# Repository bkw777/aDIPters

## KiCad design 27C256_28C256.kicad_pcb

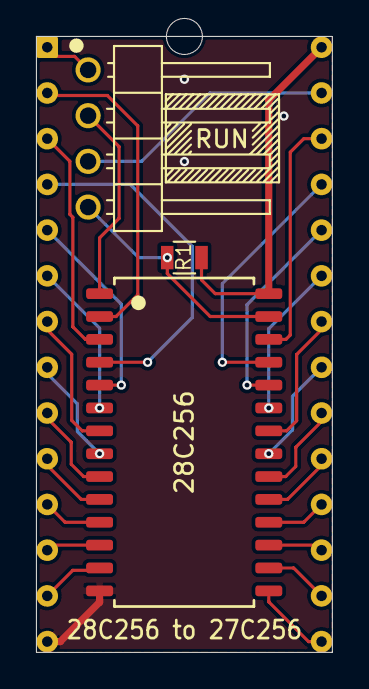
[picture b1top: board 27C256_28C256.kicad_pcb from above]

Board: 2 copper layers, 16.4 x 34.2 mm, 4 parts (0 on the bottom side), 30 nets.

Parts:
J1: 27C256 DIP LEGS; DIP-28_W15.24mm_pcb_sil_pins
JP1: Jumper_3_Bridged12; Pin_Header_Angled_1x04_Pitch2.54mm
R1: 47k; R_0805
U1: 28C256; SOIC28W

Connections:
/A0: J1.10, U1.10
/A1: J1.9, U1.9
/A2: J1.8, U1.8
/A3: J1.7, U1.7
/A4: J1.6, U1.6
/A5: J1.5, U1.5
/A6: J1.4, U1.4
/A7: J1.3, U1.3
/A8: J1.25, U1.25
/A9: J1.24, U1.24
/A10: J1.21, U1.21
/A11: J1.23, U1.23
/A12: J1.2, U1.2
/A13: J1.26, U1.26
/A14: JP1.2, U1.1
/A14_WE: J1.27, JP1.3
/D0: J1.11, U1.11
/D1: J1.12, U1.12
/D2: J1.13, U1.13
/D3: J1.15, U1.15
/D4: J1.16, U1.16
/D5: J1.17, U1.17
/D6: J1.18, U1.18
/D7: J1.19, U1.19
/GND: J1.14, U1.14
/NC_A14: J1.1, JP1.1
/VCC: J1.28, R1.2, U1.28
/~CE: J1.20, U1.20
/~OE: J1.22, U1.22
/~WE: JP1.4, R1.1, U1.27

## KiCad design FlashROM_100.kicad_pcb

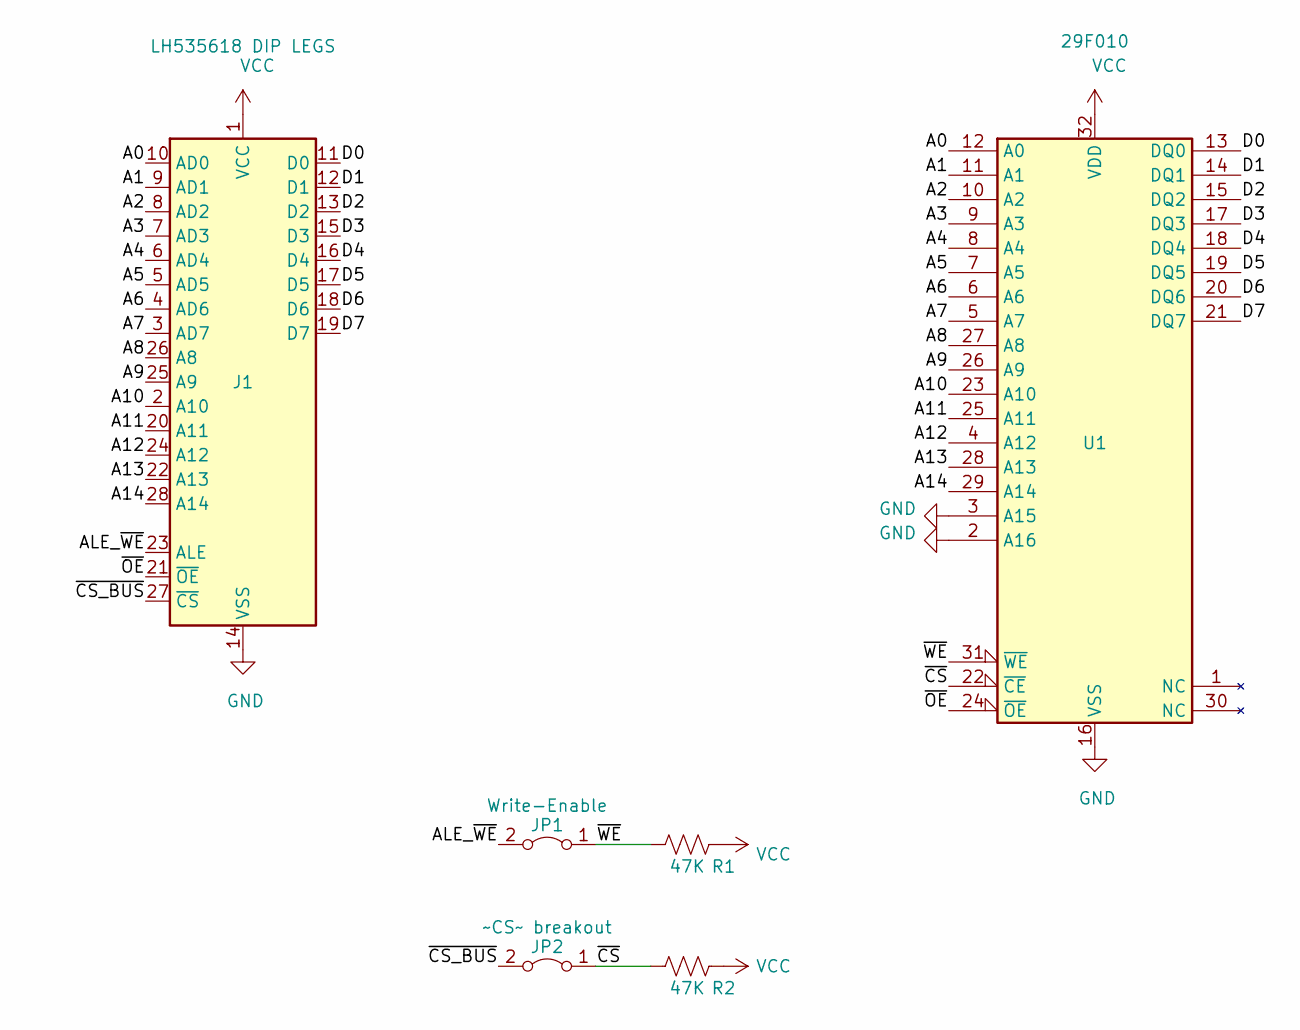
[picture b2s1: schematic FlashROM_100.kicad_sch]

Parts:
J1: LH535618 DIP LEGS; DIP28_0.6_pcb
JP1: Write-Enable; Pin_Header_Angled_1x02_Pitch2.54mm
JP2: ~CS~ breakout; Pin_Header_Angled_1x02_Pitch2.54mm
R1, R2: 47K; R_0805
U1: 29F010; PLCC32_7x9

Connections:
/A0: J1.10 (AD0), U1.12 (A0)
/A1: J1.9 (AD1), U1.11 (A1)
/A2: J1.8 (AD2), U1.10 (A2)
/A3: J1.7 (AD3), U1.9 (A3)
/A4: J1.6 (AD4), U1.8 (A4)
/A5: J1.5 (AD5), U1.7 (A5)
/A6: J1.4 (AD6), U1.6 (A6)
/A7: J1.3 (AD7), U1.5 (A7)
/A8: J1.26 (A8), U1.27 (A8)
/A9: J1.25 (A9), U1.26 (A9)
/A10: J1.2 (A10), U1.23 (A10)
/A11: J1.20 (A11), U1.25 (A11)
/A12: J1.24 (A12), U1.4 (A12)
/A13: J1.22 (A13), U1.28 (A13)
/A14: J1.28 (A14), U1.29 (A14)
/ALE_~WE: J1.23 (ALE), JP1.2 (B)
/D0: J1.11 (D0), U1.13 (DQ0)
/D1: J1.12 (D1), U1.14 (DQ1)
/D2: J1.13 (D2), U1.15 (DQ2)
/D3: J1.15 (D3), U1.17 (DQ3)
/D4: J1.16 (D4), U1.18 (DQ4)
/D5: J1.17 (D5), U1.19 (DQ5)
/D6: J1.18 (D6), U1.20 (DQ6)
/D7: J1.19 (D7), U1.21 (DQ7)
/~CS_BUS: J1.27 (~CS), JP2.2 (B)
/~CS: JP2.1 (A), R2.1, U1.22 (~CE)
/~OE: J1.21 (~OE), U1.24 (~OE)
/~WE: JP1.1 (A), R1.1, U1.31 (~WE)
GND: J1.14 (VSS), U1.2 (A16), U1.3 (A15), U1.16 (VSS)
VCC: J1.1 (VCC), R1.2, R2.2, U1.32 (VDD)

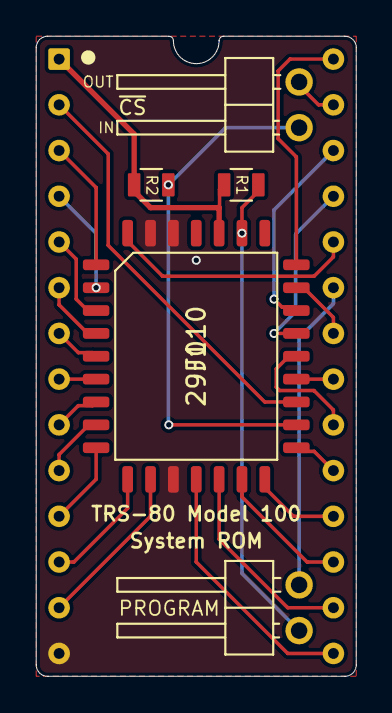
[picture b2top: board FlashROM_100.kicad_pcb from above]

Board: 2 copper layers, 17.8 x 35.6 mm, 6 parts (0 on the bottom side), 30 nets.

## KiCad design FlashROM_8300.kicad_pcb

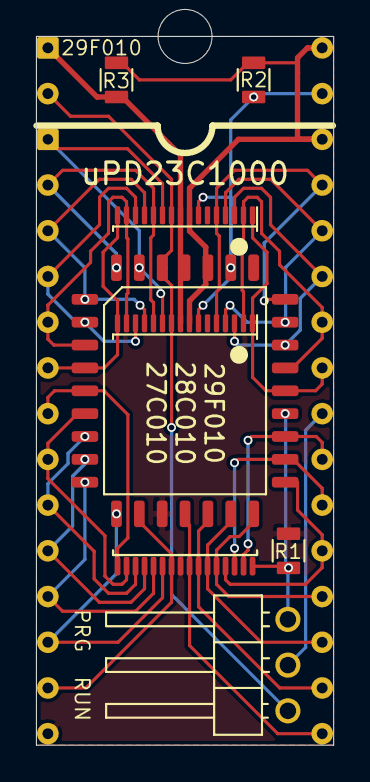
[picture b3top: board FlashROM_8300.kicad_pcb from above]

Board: 2 copper layers, 16.5 x 39.4 mm, 8 parts (0 on the bottom side), 32 nets.

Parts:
J1: uPD23C1000 / FLASH; DIP32_0.6_pcb_sil_pins
JP1: RUN/PROGRAM; Pin_Header_Angled_1x03_Pitch2.54mm_12shorted
R1: 47k; R_0805
R2, R3: 47K; R_0805
U1: 29F010 TSOP-32 20mm; TSOP32-20mm
U2: 29F010 sTSOP-32 14mm; TSOP32-14mm
U3: 29F010 PLCC 7x9; PLCC32_7x9

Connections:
/A0: J1.12, U1.20, U2.20, U3.12
/A1: J1.11, U1.19, U2.19, U3.11
/A2: J1.10, U1.18, U2.18, U3.10
/A3: J1.9, U1.17, U2.17, U3.9
/A4: J1.8, U1.16, U2.16, U3.8
/A5: J1.7, U1.15, U2.15, U3.7
/A6: J1.6, U1.14, U2.14, U3.6
/A7: J1.5, U1.13, U2.13, U3.5
/A8: J1.27, U1.3, U2.3, U3.27
/A9: J1.26, U1.2, U2.2, U3.26
/A10: J1.23, U1.31, U2.31, U3.23
/A11: J1.25, U1.1, U2.1, U3.25
/A12: J1.4, U1.12, U2.12, U3.4
/A13: J1.28, U1.4, U2.4, U3.28
/A14: J1.29, U1.5, U2.5, U3.29
/A15: J1.3, U1.11, U2.11, U3.3
/A16: J1.2, JP1.1, U1.10, U2.10, U3.2
/A16_~OE: J1.24, JP1.2
/D0: J1.13, U1.21, U2.21, U3.13
/D1: J1.14, U1.22, U2.22, U3.14
/D2: J1.15, U1.23, U2.23, U3.15
/D3: J1.17, U1.25, U2.25, U3.17
/D4: J1.18, U1.26, U2.26, U3.18
/D5: J1.19, U1.27, U2.27, U3.19
/D6: J1.20, U1.28, U2.28, U3.20
/D7: J1.21, U1.29, U2.29, U3.21
/GND: J1.16, R1.2, U1.24, U2.24, U3.16
/VCC: J1.30, J1.32, R2.2, R3.2, U1.8, U2.8, U3.32
/VPP: J1.1, R3.1, U1.9, U2.9, U3.1
/~CE: J1.22, U1.30, U2.30, U3.22
/~OE: JP1.3, R1.1, U1.32, U2.32, U3.24
/~WE: J1.31, R2.1, U1.7, U2.7, U3.31

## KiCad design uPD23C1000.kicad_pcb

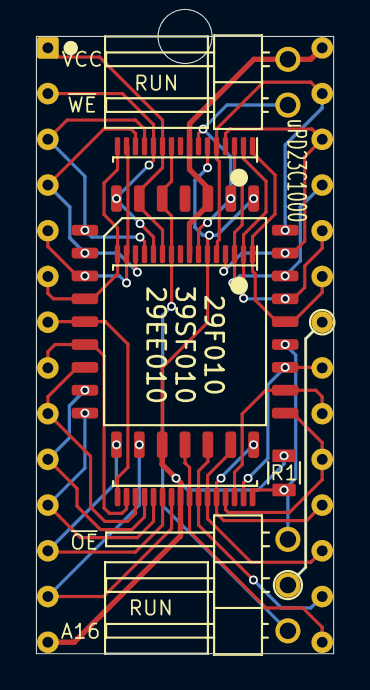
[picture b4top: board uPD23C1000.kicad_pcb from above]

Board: 2 copper layers, 16.5 x 34.3 mm, 8 parts (0 on the bottom side), 32 nets.

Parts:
J1: uPD23C1000; DIP28_0.6_pcb_sil_pins
J2: Conn_1x2; Pin_Header_Angled_1x02_Pitch2.54mm_shorted
J3: Conn_1x3; Pin_Header_Angled_1x03_Pitch2.54mm_12shorted
NT1: Net-Tie_2; NetTie-2_SMD_0.18mm
R1: 47k; R_0805
U1: 29F010 TSOP-32 20mm; TSOP32-20mm
U2: 29F010 sTSOP-32 14mm; TSOP32-14mm
U3: 29F010 PLCC-32 7x9; PLCC32_7x9

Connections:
/A0: J1.10, U1.20, U2.20, U3.12
/A1: J1.9, U1.19, U2.19, U3.11
/A2: J1.8, U1.18, U2.18, U3.10
/A3: J1.7, U1.17, U2.17, U3.9
/A4: J1.6, U1.16, U2.16, U3.8
/A5: J1.5, U1.15, U2.15, U3.7
/A6: J1.4, U1.14, U2.14, U3.6
/A7: J1.3, U1.13, U2.13, U3.5
/A8: J1.25, U1.3, U2.3, U3.27
/A9: J1.24, U1.2, U2.2, U3.26
/A10: J1.21, U1.31, U2.31, U3.23
/A11: J1.23, U1.1, U2.1, U3.25
/A12: J1.2, U1.12, U2.12, U3.4
/A13: J1.26, U1.4, U2.4, U3.28
/A14: J1.27, U1.5, U2.5, U3.29
/A15: J1.1, U1.11, U2.11, U3.3
/A16: J3.1, U1.10, U2.10, U3.2
/A16_OE: J1.22, J3.2
/A17: NT1.2, U1.6, U2.6, U3.30
/D0: J1.11, U1.21, U2.21, U3.13
/D1: J1.12, U1.22, U2.22, U3.14
/D2: J1.13, U1.23, U2.23, U3.15
/D3: J1.15, U1.25, U2.25, U3.17
/D4: J1.16, U1.26, U2.26, U3.18
/D5: J1.17, U1.27, U2.27, U3.19
/D6: J1.18, U1.28, U2.28, U3.20
/D7: J1.19, U1.29, U2.29, U3.21
/GND: J1.14, NT1.1, R1.2, U1.24, U2.24, U3.16
/VCC: J1.28, J2.2, U1.8, U2.8, U3.32
/~CE: J1.20, U1.30, U2.30, U3.22
/~OE: J3.3, R1.1, U1.32, U2.32, U3.24
/~WE: J2.1, U1.7, U2.7, U3.31

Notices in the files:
parts and their libraries:
Copyright 2016 Accelerated Designs. All rights reserved.
